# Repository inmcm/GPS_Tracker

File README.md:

# GPS_Tracker
My own little spin on a GPS tracker/logger device

## Main Components
- Controller: [Teensy 3.x]
- GPS: Adafruit [Ultimate GPS Breakout]
- Display: Adafruit [128x32 I2C OLED Display]
- Accelerometer: [ADXL345]
- LiPo Charger: [MCP73831]
- Regulator: [MIC5219]
- SD Card Socket
- Two User Buttons
- On/Off Switch
- JST Connector for LiPo Battery
- Designed to Fit inside an [Otterbox 1000 Watertight Case]

Software remains a work in progress

### Bare PCB

### Populated:

[Teensy 3.x]:https://www.pjrc.com/store/teensy31.html
[Ultimate GPS Breakout]:http://www.adafruit.com/product/746
[128x32 I2C OLED Display]:http://www.adafruit.com/product/931
[ADXL345]:https://www.sparkfun.com/products/9045
[MCP73831]:http://www.microchip.com/wwwproducts/Devices.aspx?dDocName=en024903
[MIC5219]:http://micrel.com/products/power-management-ics/ldos/single-ldos/article/85.html
[Otterbox 1000 Watertight Case]:http://www.amazon.com/OtterBox-1000-Series-Waterproof-Case/dp/B000F1ULU8

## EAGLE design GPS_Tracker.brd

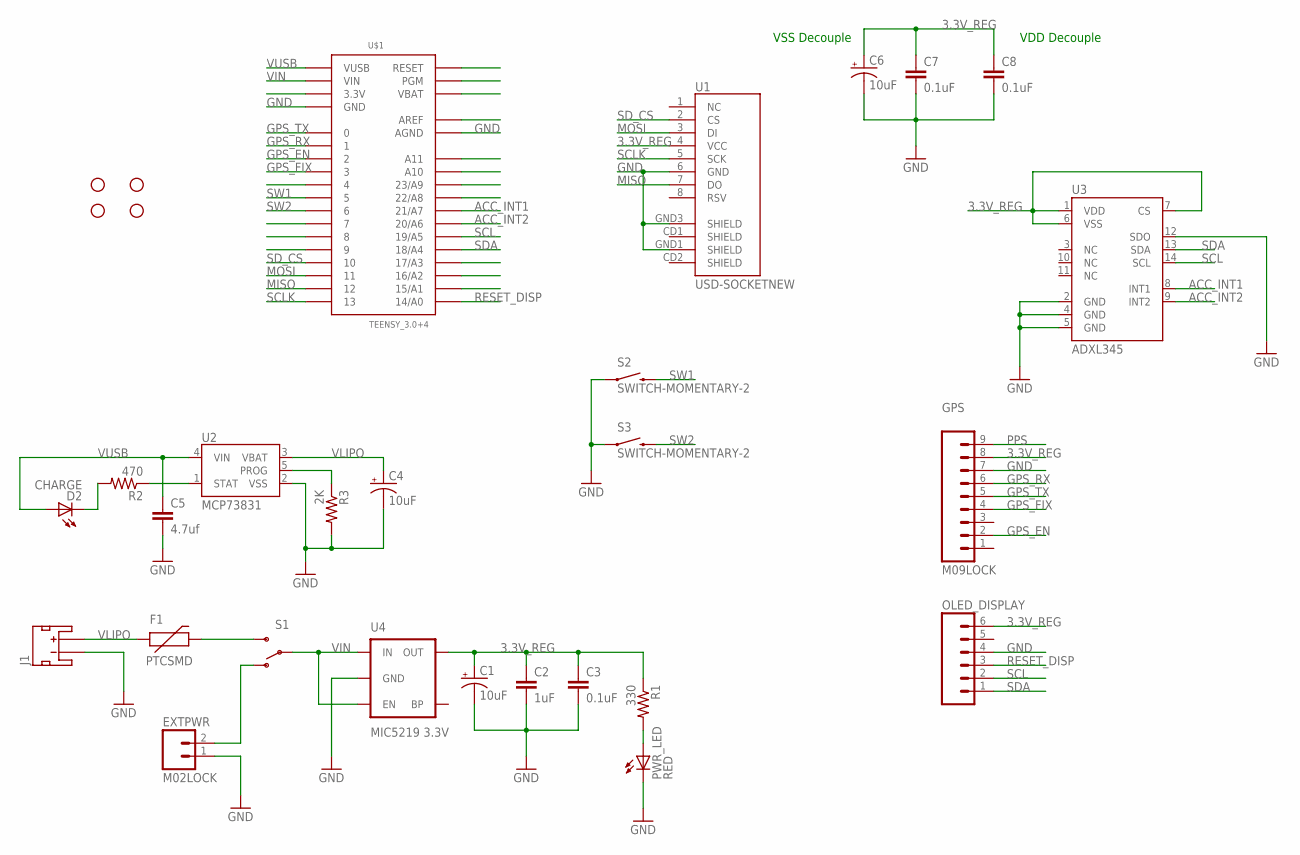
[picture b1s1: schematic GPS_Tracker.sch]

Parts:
C1, C4, C6: 10uF; EIA3216
C2: 1uF; 0402-CAP
C3, C7, C8: 0.1uF; 0402-CAP
C5: 4.7uf; 0402-CAP
D2: CHARGE; LED-0603
EXTPWR: M02LOCK; 1X02_LOCK
F1: PTCSMD; PTC-1206
GPS: M09LOCK; 1X09_LOCK
J1: JST_2MM_MALE; JST-2-SMD
OLED_DISPLAY: M06LOCK; 1X06_LOCK
PWR_LED: RED; LED-0603
R1: 330; 0402-RES
R2: 470; 0402-RES
R3: 2K; 0402-RES
S1: SWITCH-SPDTSMD; AYZ0202
S2, S3: SWITCH-MOMENTARY-2; TACTILE_SWITCH_TALL
STANDOFF1, STANDOFF2, STANDOFF3, STANDOFF4: STAND-OFF
U1: USD-SOCKETNEW; MICRO-SD-SOCKET-PP
U2: MCP73831; SOT23-5
U3: ADXL345; LGA14
U4: MIC5219 3.3V; SOT23-5
U$1: TEENSY_3.0+4

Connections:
3.3V_REG: C1.A (+), C2.1, C3.1, C6.A (+), C7.1, C8.1, GPS.8, OLED_DISPLAY.6, R1.1, U1.4 (VCC), U3.1 (VDD), U3.6 (VSS), U3.7 (CS), U4.5 (OUT)
ACC_INT1: U3.8 (INT1), U$1.21/A7
ACC_INT2: U3.9 (INT2), U$1.20/A6
GND: C1.C (-), C2.2, C3.2, C4.C (-), C5.2, C6.C (-), C7.2, C8.2, EXTPWR.1, GPS.7, J1.1 (-), OLED_DISPLAY.4, PWR_LED.C, R3.2, S2.A2 (1), S3.A2 (1), U1.6 (GND), U1.GND1 (SHIELD), U1.GND3 (SHIELD), U2.2 (VSS), U3.2 (GND), U3.4 (GND), U3.5 (GND), U3.12 (SDO), U4.2 (GND), U$1.AGND, U$1.GND, U$1.GND1 (GND)
GPS_EN: GPS.2, U$1.2
GPS_FIX: GPS.4, U$1.3
GPS_RX: GPS.6, U$1.1
GPS_TX: GPS.5, U$1.0
MISO: U1.7 (DO), U$1.12
MOSI: U1.3 (DI), U$1.11
unnamed: D2.C, R2.2
unnamed: F1.2, S1.3 (S)
unnamed: EXTPWR.2, S1.1 (O)
unnamed: U$1.3.3V, U$1.3.3V1 (3.3V)
unnamed: PWR_LED.A, R1.2
unnamed: R2.1, U2.1 (STAT)
unnamed: R3.1, U2.5 (PROG)
PPS: GPS.9
RESET_DISP: OLED_DISPLAY.3, U$1.14/A0
SCL: OLED_DISPLAY.2, U3.14 (SCL), U$1.19/A5
SCLK: U1.5 (SCK), U$1.13
SDA: OLED_DISPLAY.1, U3.13 (SDA), U$1.18/A4
SD_CS: U1.2 (CS), U$1.10
SW1: S2.B2 (2), U$1.5
SW2: S3.B2 (2), U$1.6
VIN: S1.2, U4.1 (IN), U4.3 (EN), U$1.VIN
VLIPO: C4.A (+), F1.1, J1.2 (+), U2.3 (VBAT)
VUSB: C5.1, D2.A, U2.4 (VIN), U$1.VUSB

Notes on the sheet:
VSS Decouple
VDD Decouple

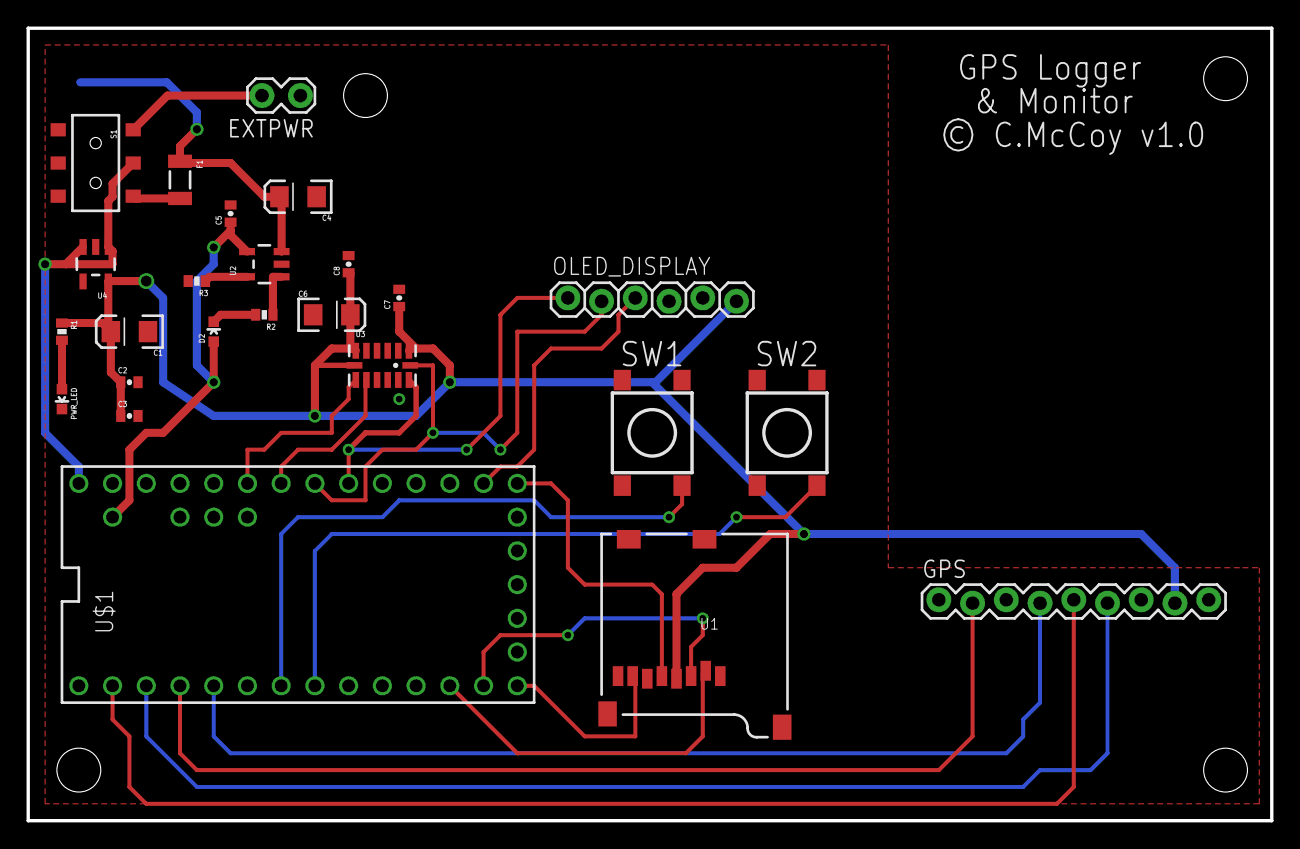
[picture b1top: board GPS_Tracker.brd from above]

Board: 2 copper layers, 93.7 x 59.7 mm, 30 parts (1 on the bottom side), 27 nets.

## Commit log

2015-02-14 Import version 1 Eagle files

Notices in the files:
GPS_Tracker.brd:
© C.McCoy v1.0
parts and their libraries:
SparkFun-Connectors: Licensing: CC v3.0 Share-Alike You are welcome to use this library for commercial purposes.
